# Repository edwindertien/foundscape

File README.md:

# foundscape
midi control of things that tap and go boink. The basic structure consists of a midi-interface that takes data from Ableton (or similar) and sends events to 'dimmer cards' - being called like that because initially they mostly controlled LED light. 

Two behaviours exist on the main board right now which can be set using a small dip switch: either pulse-lenght or pwm duty cycle as third 'velocity' argument in a MIDI command. 

current version (still in operation) uses an ATmega328 (started out with the ATmega8 and then the ATmega88 in WinAVR. now it uses the Arduino environment). In the meantime a version has been made using Teensy, but has not been further pursued / produces (when Teensies were made of nonobtanium). On the wishlist a new version with pico

## modules
- [actuators](./actuators/) 3D printfiles for solenoid holders
- [atmegaDimmer](./atmegaDimmer/) first generation dimmer/control box, using RS485(dynamixel) protocol, using ATmega328
- [RS485adapter](./RS485adapter/) RS485 - midi interface using ATmega32U4 (Arduino micro, native USB)
- [teensyDimmer](./teensyDimmer/) update of dimmer/control box, using Teensy 4.0. build, not tested
- [picoDimmer](./picoDimmer/) new (to be designed) version of the dimmer/control box using RPI Pico 2040/2350

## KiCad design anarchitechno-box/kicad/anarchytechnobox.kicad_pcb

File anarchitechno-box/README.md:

# foundscape electronics

## anarchitechno box (formerly known as 'pico dimmer')

The boxes are still called 'dimmer' since all channels can either be switched (solenoids, pneumatic valves) where the control parameter is a pulse duration (so short sharp tap or long, plungy tap - and everything in between) or a PWM value (used typically for LED brightness or motor velocity),

During a session at Koppelting (Amersfoort) in August 2025 we found that a very interesting additiion in just 'dimming' channels is also PWM (frequency) control and AWG / synthesis to make actuators sound even more. During the session the requirements below have been updated and start has been made with a new (schematic) design. 

On the wishlist for the next design (using for example the atmega version or the teensy version as starting point)

### power
- multiple voltages for output, would be nice to change per channel, but for now typically 1 output voltage (i.e. 12V) per channel is fine. It would be nice when the system can work on 12V, but also as low as 5V and at least at 24V
- 8 channels, individual control mode per channel for one-shot (solenoids, timing), PWM (frequency, duty cycle) and AWG (saw/sine/triangle/block/noise, frequency, phase, amplitude)
- polyfuse per channel, Fuse indicator
- 1 LED per channel (indication)
- flyback diodes per channel
- TVS, power supply protection, main fuse

not yet implemented but nice to have
- power monitoring (voltage / current)
- reverse voltage protection

For now the output section consisting of IRFZ44 and TC4423 has been working ok. Might be room to revise for newer, cheaper and SMD version. See if gate driver is necessary, but might be for higher switching frequencies. I checked other gate drivers, so far the 4427 seems a good (SMD) follow up with a good balance in price, performance and size

### power
Right now I tend to put in a Traco power TC2450 or similar to do the 12-24V to 5V conversion. Might be up for a change too. 

It wouls be very welcome to have galvanic separation between the power stage (12-24V side) and the logic side. The power consumption at the logic side is non-neglegible:
- pico (3.3V) - 20 mA? 
- OLED .. mA
- WS5500 .. mA
- USB Host -> 500mA

It might be best to build a 5Watt (1A) switching power supply or use a ready to go module. The TI 6505B uses a separate transformer (suggested, but need to be checked ) [wurth](https://octopart.com/750313974-wurth+electronics+midcom-49417564) and can go up to 5 Watt.

### galvanic separation
- using isolators it is important to separate the high/power (24V) side from the logic side. This means digital isolators as well as an isiolated 5V->5.5V supply. The USB Host needs 5V, the pico can do 5V->3.3V with its on-board converter

### brains
- pico (2W) - might be the standard board, or just the RP2040 or RP2350 chip + necessary peripherals
- OLED (small 32x128 pix) is very useful for menu, status info etc
- incremental encoder (3 switches) - pio code works fine. good for changing menu options
- simple basic LEDs on power and communication lines (so you can always check com, also when you are fiddeling with a menu), also from a distance. 
- WS8211 RGB leds (string), 1 per channel (channel mode selection) and communication status (per socket / unit)

### connection
- USB (midi, serial)  -> existing USB micro
- USB Host (midi, gamepad, HID) -> add USB A socket. Think about necessary series resistors and power components. 
- RS485 (DMX: neutrix 3/5 pin, 'dynamixel' bus) -> 3way(A, B, GND) and 4way (A, B, Power, GND) jst socket. For (my) RJ45 and a neutrik socket we can make an adapter? Or have the RJ45 system since it is so easy to stack through.. 
- ethernet: WSD5500 + socket + mag
- MIDI: old fashioned 5-pin DIN midi (CNY138 optocoupler) (can also be adapter cable from 5-way jst socket)
- A pico could in theory also do everything WIFI / Bluetooth / BLE wise. .. 
- HW sync input (optocoupler?)

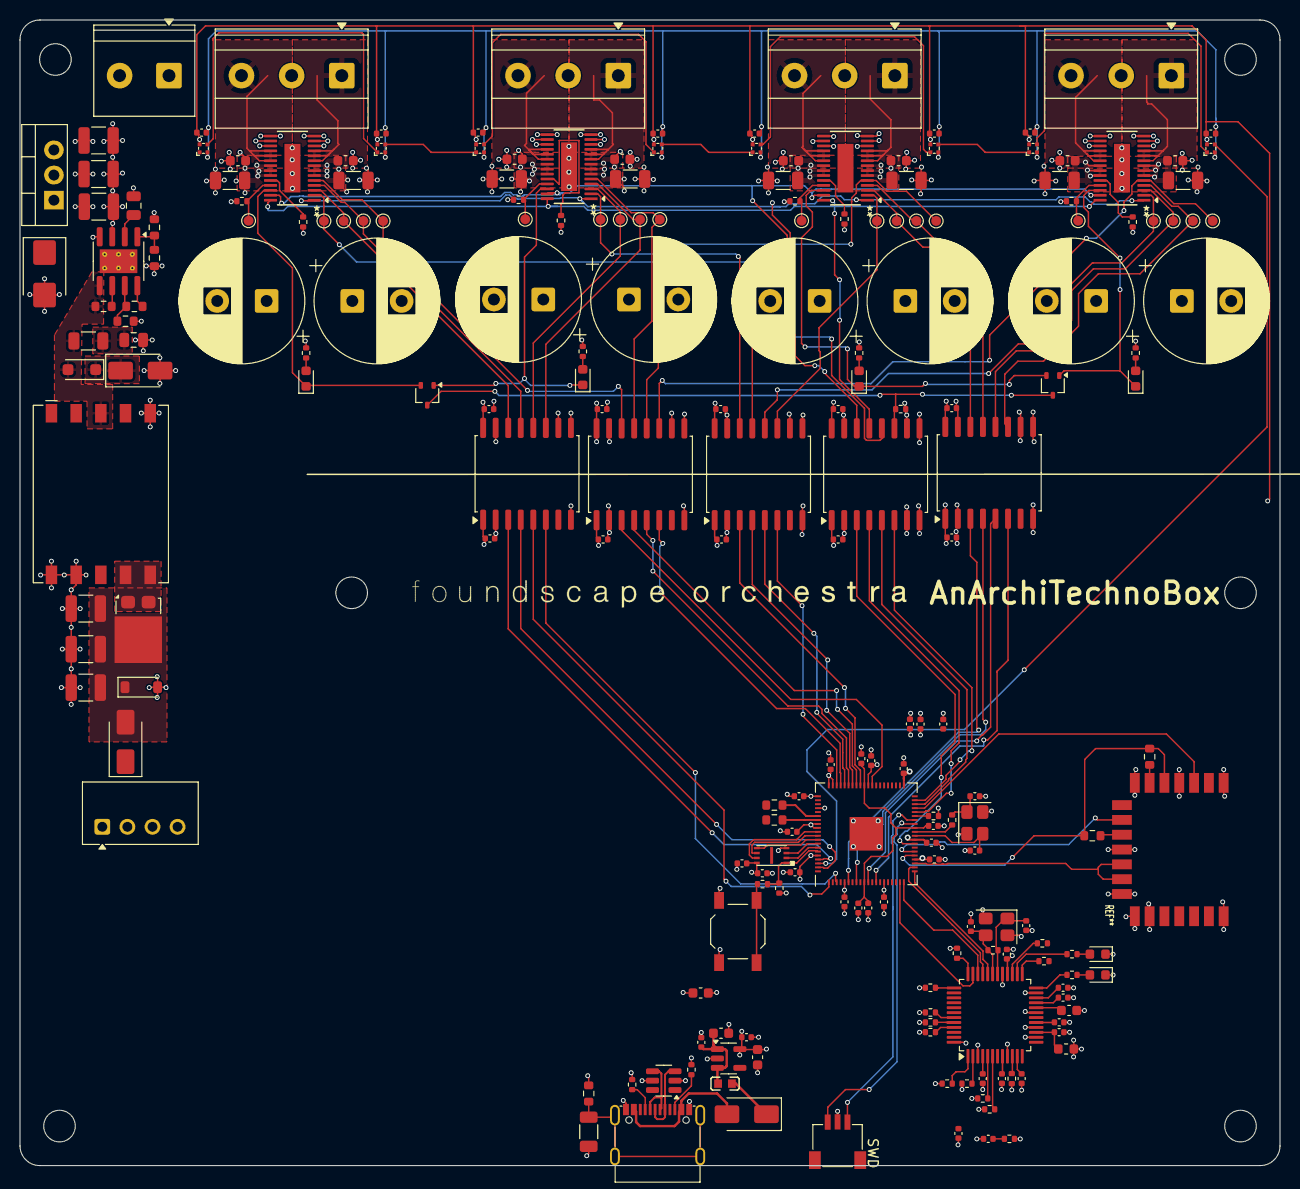
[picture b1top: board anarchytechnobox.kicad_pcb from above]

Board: 4 copper layers, 127.6 x 116.0 mm, 216 parts (0 on the bottom side), 144 nets.

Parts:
C1, C2, C3, C4, C5, C7, C8, C11, C13, C14, C15, C16, C21, C22, C23, C27, C30, C31, C32, C33, C46, C47, C48, C49, C50, C51, C54, C55, C56, C58, C60, C61, C62, C86, C87, C88, C89, C90, C91: 100nF; C_0402_1005Metric
C6: 4.7u; C_0402_1005Metric
C9, C17: 100n; C_0402_1005Metric
C10, C18, C19: 1u; C_0402_1005Metric
C12, C20, C26: 10uF; C_0603_1608Metric
C24: 4.7n 100v; C_1206_3216Metric
C25: 0.1uF; C_0402_1005Metric
C28, C29: 27p; C_0402_1005Metric
C34, C35, C40, C41, C74, C75, C80, C81: 1uF 50V; C_0603_1608Metric
C36, C37, C42, C43, C76, C77, C82, C83: 10uF 50V; C_1206_3216Metric
C38, C39, C44, C45, C78, C79, C84, C85: 1000uF 50V; CP_Radial_D12.5mm_P5.00mm
C52, C53: 15p; C_0402_1005Metric
C57: 10nF; C_0402_1005Metric
C59: 4.7uF; C_0603_1608Metric
C63: 22n; C_0402_1005Metric
C64: 10n; C_0402_1005Metric
C65: 330uF 50V; C_1210_3225Metric
C66, C67: 10uF 50V; C_1210_3225Metric
C68: 1uF 25V; C_0805_2012Metric
C69: 220pF; C_0805_2012Metric
C70, C71, C72: 47uF 10V; C_1210_3225Metric
D1: SM6T24A; D_SMB
D2, D3, D18, D19, D20, D21, D22, D23: C5349953; XL-1010
D4, D5: BAT54AW; SOT-323_SC-70
D6, D7, D8, D9, D14, D15: RED; LED_0603_1608Metric
D10: SMAJ18A; D_SMA
D11: CMMSH1-100; D_SOD-123F
D12: V8PM10SHM3/I; TO-277A
D13: CMHZ5232B; D_SOD-123
D16, D17: SS34; D_SMA
FB1: BLM18PG121SN1D; L_0603_1608Metric
H1, H2, H3, H4, H5, H6: MountingHole; MountingHole_3.2mm_M3
J1: C2988369; USB-C C2988369
J2: Conn_01x03_Socket; SWD_TOP
J3, J4, J5, J6: Screw_Terminal_01x03; TerminalBlock_Phoenix_MKDS-1,5-3-5.08_1x03_P5.08mm_Horizont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
J7: Screw_Terminal_01x02; TerminalBlock_Phoenix_PT-1,5-2-5.0-H_1x02_P5.00mm_Horizontal
L1: BLM18PG121SN1D_C14709; L0603
Q1: 12mhz; Crystal_SMD_SeikoEpson_TSX3225-4Pin_3.2x2.5mm
R1: 470; R_0603_1608Metric
R2: 10k; R_0603_1608Metric
R3: 1M; R_0603_1608Metric
R4, R5: 5.1k; R_0402_1005Metric
R6, R10: 10k; R_0402_1005Metric
R7, R8: 27; R_0603_1608Metric
R9, R11: 1k; R_0402_1005Metric
R12, R15, R25, R26, R27, R28, R41, R44: 470R; R_0402_1005Metric
R13, R16, R42, R45: 0R; R_0402_1005Metric
R14, R17, R43, R46: TBD; R_0402_1005Metric
R18: 10K; R_0402_1005Metric
R19: 1MEG; R_0402_1005Metric
R20, R21, R22, R23, R24: 1K; R_0402_1005Metric
R29: 12.4k; R_0402_1005Metric
R30, R31, R33, R34: 49R9; R_0402_1005Metric
R32: 10R; R_0402_1005Metric
R35: 1MEG; R_0603_1608Metric
R36: 200K; R_0603_1608Metric
R37: 150K; R_0603_1608Metric
R38: 113K; R_0603_1608Metric
R39: 100R; R_1206_3216Metric
R40: 10K; R_0603_1608Metric
SW1: C318884; SW_SPST_TL3342
TP1, TP2, TP3, TP4, TP5, TP6, TP7, TP8, TP9, TP10, TP11, TP12, TP13, TP14, TP15, TP16, TP17, TP18, TP19, TP20: TestPoint; TestPoint_Pad_D1.0mm
U1: TME-0503S; Converter_DCDC_TRACO_TME_03xxS_05xxS_12xxS_Single_THT
U3: LM7812_TO220; TO-220-3_Vertical
U4: <value>; rpi_rmc20452t
U5: LP5907MFX-3.3; SOT-23-5
U7: C85364; SOT-23-6
U8: QFN-80_EP_10x10_Pitch0.4mm
U9, U10, U13, U14: ISO7740DWR; SOIC-16W_7.5x10.3mm_P1.27mm
U11, U12, U20, U21: DRV8243SQDGQRQ1; TI_HVSSOP-28
U15: ISO7742DWR; SOIC-16W_7.5x10.3mm_P1.27mm
U16: W5500; LQFP-48_7x7mm_P0.5mm
U18: ADPL54203ES8E#PBF; SOIC-8-1EP_3.9x4.9mm_P1.27mm_EP2.41x3.81mm_ThermalVias
U19: 750311564; T_Wurth_WE-FB-EP13_16.36
U$1: C2843335 W25Q16JVUXIQ; USON-8-EP(2x3)
Y1: 25MHz; Crystal_SMD_3225-4Pin_3.2x2.5mm

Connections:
+1V1: C18.2, C19.1, C21.1, C22.2, C23.1, U8.10 (DVDD), U8.32 (DVDD), U8.51 (DVDD)
+3.3VA: C55.1, C56.1, C58.1, C60.1, C61.1, C62.1, FB1.2, U16.4 (AVDD), U16.8 (AVDD), U16.11 (AVDD), U16.15 (AVDD), U16.17 (AVDD), U16.21 (AVDD)
+3.3VP: C31.1, C33.1, C49.1, C50.1, C51.1, R12.1, R13.1, R15.1, R16.1, R18.1, R41.1, R42.1, R44.1, R45.1, U9.10 (EN2), U9.16 (VCC2), U10.10 (EN2), U10.16 (VCC2), U13.10 (EN2), U13.16 (VCC2), U14.10 (EN2), U14.16 (VCC2), U15.10 (EN2), U15.16 (VCC2)
+3V3: C1.2, C2.2, C3.2, C4.2, C5.2, C6.1, C7.2, C8.2, C10.2, C11.2, C13.2, C14.2, C15.2, C16.2, C17.2, C20.1, C25.1, C26.1, C27.2, C30.1, C32.1, C46.1, C47.1, C48.1, C54.1, C86.2, C87.2, C88.2, C89.2, C90.2, C91.2, D2.2 (VDD), D3.2 (VDD), D18.2 (VDD), D19.2 (VDD), D20.2 (VDD), D21.2 (VDD), D22.2 (VDD), D23.2 (VDD), FB1.1, R6.2, R10.1, R20.1, R21.1, R22.1, R23.2, R24.2, R30.1, R31.1, R32.1, R33.1, R34.1, U4.14 (VDDIO), U4.16 (VIN), U5.5 (OUT), U7.5 (REF), U8.5 (IOVDD), U8.15 (IOVDD), U8.24 (IOVDD), U8.29 (IOVDD), U8.41 (IOVDD), U8.50 (IOVDD), U8.59 (ADC_IOVDD), U8.60 (IOVDD), U8.61 (VREG_AVDD), U8.64 (VREG_VIN), U8.68 (USB_OTP_VDD), U8.69 (QSPI_IOVDD), U8.76 (IOVDD), U9.1 (VCC1), U10.1 (VCC1), U13.1 (VCC1), U14.1 (VCC1), U15.1 (VCC1), U15.7 (EN1), U16.28 (VDD), U$1.8 (VCC)
+5V: D16.1 (K), D17.1 (K), L1.1, U1.2 (+Vin)
+24V: D1.1 (A1), U3.1 (VI)
+VDC: C34.1, C35.1, C36.1, C37.1, C38.1, C39.1, C40.1, C41.1, C42.1, C43.1, C44.1, C45.1, C65.1 (+), C66.1 (+), C67.1 (+), C69.1 (+), C74.1, C75.1, C76.1, C77.1, C78.1, C79.1, C80.1, C81.1, C82.1, C83.1, C84.1, C85.1, D10.2 (A), J7.1, R35.2 (-), U11.6 (VM), U11.7 (VM), U11.8 (VM), U11.21 (VM), U11.22 (VM), U11.23 (VM), U12.6 (VM), U12.7 (VM), U12.8 (VM), U12.21 (VM), U12.22 (VM), U12.23 (VM), U18.3 (VIN), U19.5 (N1_2), U20.6 (VM), U20.7 (VM), U20.8 (VM), U20.21 (VM), U20.22 (VM), U20.23 (VM), U21.6 (VM), U21.7 (VM), U21.8 (VM), U21.21 (VM), U21.22 (VM), U21.23 (VM)
/DCDC Flyback/PRE_5V: C70.1 (+), C71.1 (+), C72.1 (+), D12.3 (K), D13.1 (K), D17.2 (A)
/DCDC Flyback/PRE_PRE_5V: D12.1 (A), D12.2 (A), U19.6 (N2_1), U19.7 (N2_1)
/DCDC Flyback/VDC_CAPRES: C69.2 (-), R39.1 (+)
/DCDC Flyback/VDC_DIODES: D10.1 (K), D11.1 (K)
/DCDC Flyback/VDC_SW: D11.2 (A), R37.2 (-), R39.2 (-), U18.5 (SW), U19.3 (N1_1)
/Ethernet/ETH_RX_M: R34.2, U16.5 (RXN)
/Ethernet/ETH_RX_P: R33.2, U16.6 (RXP)
/Ethernet/ETH_TX_M: R31.2, U16.1 (TXN)
/Ethernet/ETH_TX_P: R30.2, U16.2 (TXP)
/Ethernet/SPI_CS: U8.21 (GPIO21), U16.32 (~SCS)
/Ethernet/SPI_INT: R23.1, U16.36 (~INT)
/Ethernet/SPI_MISO: U8.20 (GPIO20), U16.34 (MISO)
/Ethernet/SPI_MOSI: U8.19 (GPIO19), U16.35 (MOSI)
/Ethernet/SPI_RST: R24.1, U16.37 (~RST)
/Ethernet/SPI_SCK: U8.22 (GPIO22), U16.33 (SCLK)
/HB_1_OUT_A: J3.1, U20.9 (OUT1), U20.10 (OUT1), U20.11 (OUT1)
/HB_1_OUT_B: J3.3, U20.18 (OUT2), U20.19 (OUT2), U20.20 (OUT2)
/HB_1_OUT_C: J4.1, U21.9 (OUT1), U21.10 (OUT1), U21.11 (OUT1)
/HB_1_OUT_D: J4.3, U21.18 (OUT2), U21.19 (OUT2), U21.20 (OUT2)
/HB_2_OUT_A: J5.1, U11.9 (OUT1), U11.10 (OUT1), U11.11 (OUT1)
/HB_2_OUT_B: J5.3, U11.18 (OUT2), U11.19 (OUT2), U11.20 (OUT2)
/HB_2_OUT_C: J6.1, U12.9 (OUT1), U12.10 (OUT1), U12.11 (OUT1)
/HB_2_OUT_D: J6.3, U12.18 (OUT2), U12.19 (OUT2), U12.20 (OUT2)
/Isolators/MCU_CS1: U8.52 (GPIO41_ADC1), U14.3 (INA)
/Isolators/MCU_CS2: U8.54 (GPIO43_ADC3), U14.4 (INB)
/Isolators/MCU_CS3: U8.56 (GPIO45_ADC5), U14.5 (INC)
/Isolators/MCU_CS4: U8.58 (GPIO47_ADC7), U14.6 (IND)
/Isolators/MCU_DRV_nFAULT_COMMON: U8.39 (GPIO31), U15.6 (OUTD)
/Isolators/MCU_PWM_A_OFF: U8.49 (GPIO40_ADC0), U13.3 (INA)
/Isolators/MCU_PWM_B_OFF: U8.53 (GPIO42_ADC2), U13.4 (INB)
/Isolators/MCU_PWM_C_OFF: U8.55 (GPIO44_ADC4), U13.5 (INC)
/Isolators/MCU_PWM_D_OFF: U8.57 (GPIO46_ADC6), U13.6 (IND)
/Isolators/MCU_SPI_CLK: U8.28 (GPIO27), U15.3 (INA)
/Isolators/MCU_SPI_MISO: U8.38 (GPIO30), U15.5 (OUTC)
/Isolators/MCU_SPI_MOSI: U8.36 (GPIO28), U15.4 (INB)
/Isolators/PWR_DRV_nFAULT_COMMON: D4.3, D5.3, R18.2, U15.11 (IND)
/Isolators/PWR_PWM_A_OFF: TP19.1, U13.14 (OUTA), U21.5 (DRVOFF)
/Isolators/PWR_PWM_B_OFF: TP14.1, U13.13 (OUTB), U20.5 (DRVOFF)
/Isolators/PWR_PWM_C_OFF: TP9.1, U12.5 (DRVOFF), U13.12 (OUTC)
/Isolators/PWR_PWM_D_OFF: TP4.1, U11.5 (DRVOFF), U13.11 (OUTD)
/Isolators/PWR_SPI_CLK: U11.1 (SCLK), U12.1 (SCLK), U15.14 (OUTA), U20.1 (SCLK), U21.1 (SCLK)
/Isolators/PWR_SPI_CS1: TP15.1, U14.14 (OUTA), U20.2 (nSCS)
/Isolators/PWR_SPI_CS2: TP20.1, U14.13 (OUTB), U21.2 (nSCS)
/Isolators/PWR_SPI_CS3: TP5.1, U11.2 (nSCS), U14.12 (OUTC)
/Isolators/PWR_SPI_CS4: TP10.1, U12.2 (nSCS), U14.11 (OUTD)
/Isolators/PWR_SPI_MISO: U11.27 (SDO), U12.27 (SDO), U15.12 (INC), U20.27 (SDO), U21.27 (SDO)
/Isolators/PWR_SPI_MOSI: U11.28 (SDI), U12.28 (SDI), U15.13 (OUTB), U20.28 (SDI), U21.28 (SDI)
/LED_STRING: D2.4 (DI), U8.78 (GPIO1)
/RP2350BMCU/5V_filtered: C9.2, C12.1, L1.2, U5.1 (IN), U5.3 (EN)
/RP2350BMCU/BOOTSEL_BUT: R9.2, SW1.2
/RP2350BMCU/BREAKOUT_5V: D16.2 (A), J1.A4B9 (VBUS), J1.A9B4 (VBUS)
/RP2350BMCU/MEM_CLK: U8.71 (QSPI_SCLK), U$1.6 (CLK)
/RP2350BMCU/MEM_CS: R6.1, R9.1, U8.75 (QSPI_SS), U$1.1 (/CS)
/RP2350BMCU/MEM_IO0: U8.72 (QSPI_SD0), U$1.5 (DI)
/RP2350BMCU/MEM_IO1: U8.74 (QSPI_SD1), U$1.2 (DO)
/RP2350BMCU/MEM_IO2: U8.73 (QSPI_SD2), U$1.3 (IO2)
/RP2350BMCU/MEM_IO3: U8.70 (QSPI_SD3), U$1.7 (IO3)
/RP2350BMCU/PMW1_A: U8.79 (GPIO2), U9.4 (INB)
/RP2350BMCU/PWM0_A: U8.77 (GPIO0), U9.3 (INA)
/RP2350BMCU/PWM2_A: U8.1 (GPIO4), U9.5 (INC)
/RP2350BMCU/PWM3_A: U8.3 (GPIO6), U9.6 (IND)
/RP2350BMCU/PWM4_A: U8.6 (GPIO8), U10.3 (INA)
/RP2350BMCU/PWM5_A: U8.8 (GPIO10), U10.4 (INB)
/RP2350BMCU/PWM6_A: U8.11 (GPIO12), U10.5 (INC)
/RP2350BMCU/PWM7_A: U8.13 (GPIO14), U10.6 (IND)
/RP2350BMCU/RUN: R10.2, U8.35 (RUN)
/RP2350BMCU/SWCLK: J2.1, U8.33 (SWCLK)
/RP2350BMCU/SWDIO: J2.3, U8.34 (SWD)
/RP2350BMCU/USB_N: J1.A7 (DN1), J1.B7 (DN2), R8.1, U7.4 (IO3)
/RP2350BMCU/USB_P: J1.A6 (DP1), J1.B6 (DP2), R7.1, U7.3 (IO2)
/RP2350BMCU/USB_PRE_N: R8.2, U8.66 (USB_DN)
/RP2350BMCU/USB_PRE_P: R7.2, U8.67 (USB_DP)
/RP2350BMCU/WIFI_23: U4.12 (WL_ON), U4.13 (BT_ON), U8.23 (GPIO23)
/RP2350BMCU/WIFI_24: R1.2, R2.2, U4.5 (DI), U8.25 (GPIO24)
/RP2350BMCU/WIFI_25: U4.9 (CS), U8.26 (GPIO25)
/RP2350BMCU/WIFI_29: U4.3 (SCLK), U8.37 (GPIO29)
/TwoIsolatedFETs0/HBridge_A/DRV_ISENSE: R46.1, TP16.1, U21.25 (IPROPI)
/TwoIsolatedFETs0/HBridge_A/DRV_nFAULT: D4.2, D15.1 (K), U21.26 (nFAULT)
/TwoIsolatedFETs0/HBridge_B/DRV_ISENSE: R43.1, TP11.1, U20.25 (IPROPI)
/TwoIsolatedFETs0/HBridge_B/DRV_nFAULT: D4.1, D14.1 (K), U20.26 (nFAULT)
/TwoIsolatedFETs0/PWM_A_1: TP18.1, U9.13 (OUTB), U21.4 (EN/IN1)
/TwoIsolatedFETs0/PWM_A_2: TP17.1, U9.14 (OUTA), U21.3 (PH/IN2)
/TwoIsolatedFETs0/PWM_B_1: TP13.1, U9.11 (OUTD), U20.4 (EN/IN1)
/TwoIsolatedFETs0/PWM_B_2: TP12.1, U9.12 (OUTC), U20.3 (PH/IN2)
/TwoIsolatedFETs1/HBridge_A/DRV_ISENSE: R17.1, TP6.1, U12.25 (IPROPI)
/TwoIsolatedFETs1/HBridge_A/DRV_nFAULT: D5.2, D7.1 (K), U12.26 (nFAULT)
/TwoIsolatedFETs1/HBridge_B/DRV_ISENSE: R14.1, TP1.1, U11.25 (IPROPI)
/TwoIsolatedFETs1/HBridge_B/DRV_nFAULT: D5.1, D6.1 (K), U11.26 (nFAULT)
/TwoIsolatedFETs1/PWM_A_1: TP8.1, U10.13 (OUTB), U12.4 (EN/IN1)
/TwoIsolatedFETs1/PWM_A_2: TP7.1, U10.14 (OUTA), U12.3 (PH/IN2)
/TwoIsolatedFETs1/PWM_B_1: TP3.1, U10.11 (OUTD), U11.4 (EN/IN1)
/TwoIsolatedFETs1/PWM_B_2: TP2.1, U10.12 (OUTC), U11.3 (PH/IN2)
GND: C1.1, C2.1, C3.1, C4.1, C5.1, C6.2, C7.1, C8.1, C9.1, C10.1, C11.1, C12.2, C13.1, C14.1, C15.1, C16.1, C17.1, C18.1, C19.2, C20.2, C21.2, C22.1, C23.2, C24.1, C25.2, C26.2, C27.1, C28.2, C29.2, C30.2, C32.2, C46.2, C47.2, C48.2, C52.2, C53.2, C54.2, C55.2, C56.2, C57.2, C58.2, C59.2, C60.2, C61.2, C62.2, C63.1, C64.1, C70.2 (-), C71.2 (-), C72.2 (-), C86.1, C87.1, C88.1, C89.1, C90.1, C91.1, D2.3 (GND), D3.3 (GND), D8.1 (K), D9.1 (K), D13.2 (A), D18.3 (GND), D19.3 (GND), D20.3 (GND), D21.3 (GND), D22.3 (GND), D23.3 (GND), J1.A1B12 (GND), J1.A12B1 (GND), J2.2, Q1.2 (G2), Q1.4 (G1), R3.1, R4.2, R5.2, R29.2, SW1.1, U1.3 (-Vout), U4.1 (GND), U4.4 (GND), U4.7 (GND), U4.11 (GND), U4.15 (GND), U4.21 (GND), U5.2 (GND), U7.2 (GND), U8.81 (GND), U9.2 (GND1), U9.8 (GND1), U10.2 (GND1), U10.8 (GND1), U13.2 (GND1), U13.8 (GND1), U14.2 (GND1), U14.8 (GND1), U15.2 (GND1), U15.8 (GND1), U16.3 (AGND), U16.9 (AGND), U16.14 (AGND), U16.16 (AGND), U16.19 (AGND), U16.23 (RSVD), U16.29 (GND), U16.48 (AGND), U19.9 (N2_2), U19.10 (N2_2), U$1.4 (GND), Y1.2, Y1.4
GND2: C31.2, C33.2, C34.2, C35.2, C36.2, C37.2, C38.2, C39.2, C40.2, C41.2, C42.2, C43.2, C44.2, C45.2, C49.2, C50.2, C51.2, C65.2 (-), C66.2 (-), C67.2 (-), C68.2 (-), C74.2, C75.2, C76.2, C77.2, C78.2, C79.2, C80.2, C81.2, C82.2, C83.2, C84.2, C85.2, D1.2 (A2), J3.2, J4.2, J5.2, J6.2, J7.2, R14.2, R17.2, R36.1 (+), R40.2 (-), R43.2, R46.2, U1.1 (-Vin), U3.2 (GND), U9.9 (GND2), U9.15 (GND2), U10.9 (GND2), U10.15 (GND2), U11.12 (GND), U11.13 (GND), U11.14 (GND), U11.15 (GND), U11.16 (GND), U11.17 (GND), U11.EP (GND), U12.12 (GND), U12.13 (GND), U12.14 (GND), U12.15 (GND), U12.16 (GND), U12.17 (GND), U12.EP (GND), U13.9 (GND2), U13.15 (GND2), U14.9 (GND2), U14.15 (GND2), U15.9 (GND2), U15.15 (GND2), U18.4 (GND), U18.9 (GND), U20.12 (GND), U20.13 (GND), U20.14 (GND), U20.15 (GND), U20.16 (GND), U20.17 (GND), U20.EP (GND), U21.12 (GND), U21.13 (GND), U21.14 (GND), U21.15 (GND), U21.16 (GND), U21.17 (GND), U21.EP (GND)
unnamed: C24.2, J1.SHELL1, J1.SHELL2, J1.SHELL3, J1.SHELL4, R3.2
unnamed: C68.1 (+), U18.2 (INTVCC)
unnamed: D2.1 (DO), D3.4 (DI)
unnamed: D6.2 (A), R12.2
unnamed: D7.2 (A), R15.2
unnamed: D8.2 (A), R25.2
unnamed: D9.2 (A), R27.2
unnamed: D14.2 (A), R41.2
unnamed: D15.2 (A), R44.2
unnamed: D3.1 (DO), D18.4 (DI)
unnamed: D18.1 (DO), D19.4 (DI)
unnamed: D19.1 (DO), D20.4 (DI)
unnamed: D20.1 (DO), D21.4 (DI)
unnamed: D21.1 (DO), D22.4 (DI)
unnamed: D22.1 (DO), D23.4 (DI)
unnamed: J1.A5 (CC1), R4.1
unnamed: J1.B5 (CC2), R5.1
unnamed: C28.1, Q1.1 (X1), R11.1
unnamed: C29.1, Q1.3 (X2), U8.30 (XIN)
unnamed: R35.1 (+), R36.2 (-), U18.1 (EN/UVLO)
unnamed: R37.1 (+), U18.6 (RFB)
unnamed: R38.1 (+), U18.8 (TC)
unnamed: R38.2 (-), R40.1 (+), U18.7 (RREF)
unnamed: R1.1, U4.6 (DO)
unnamed: R2.1, U4.10 (nIRQ)
unnamed: R11.2, U8.31 (XOUT)
unnamed: R13.2, U11.24 (nSLEEP)
unnamed: R16.2, U12.24 (nSLEEP)
unnamed: C57.1, U16.22 (1V2O)
unnamed: R28.1, U16.27 (ACTLED)
unnamed: R27.1, U16.26 (DUPLED)
unnamed: R29.1, U16.10 (EXRES1)
unnamed: R26.1, U16.25 (LINKLED)
unnamed: R20.2, U16.45 (PMODE0)
unnamed: R21.2, U16.44 (PMODE1)
unnamed: R22.2, U16.43 (PMODE2)
unnamed: R25.1, U16.24 (SPDLED)
unnamed: C59.1, U16.20 (TOCAP)
unnamed: C52.1, R19.2, U16.30 (XI/CLKIN), Y1.1
unnamed: C53.1, R19.1, U16.31 (XO), Y1.3
unnamed: C63.2, R32.2
unnamed: R42.2, U20.24 (nSLEEP)
unnamed: R45.2, U21.24 (nSLEEP)

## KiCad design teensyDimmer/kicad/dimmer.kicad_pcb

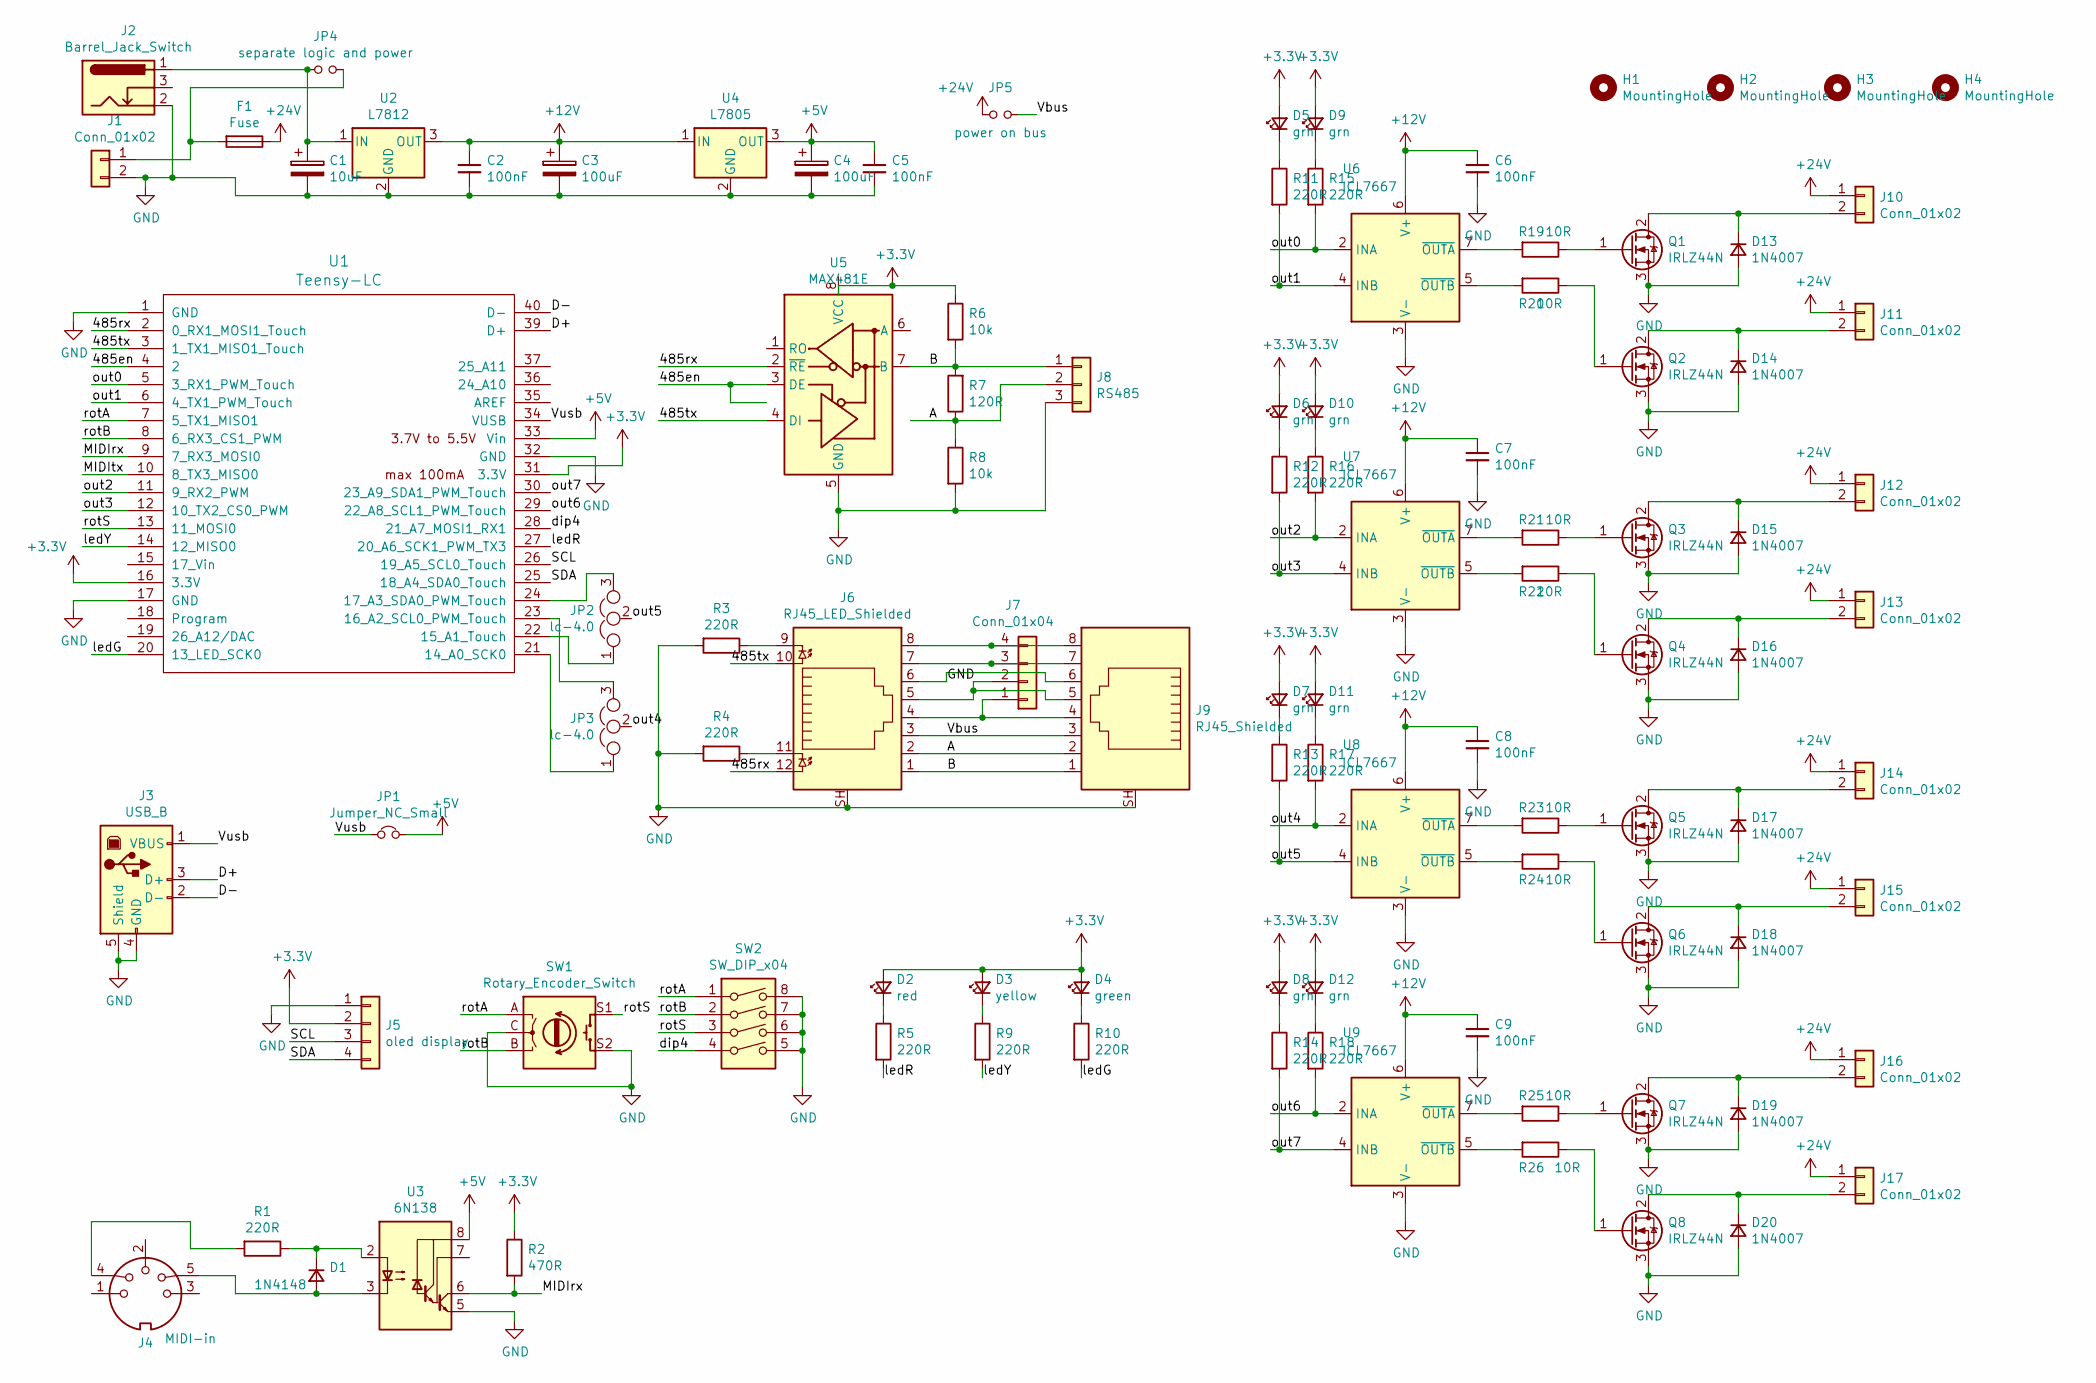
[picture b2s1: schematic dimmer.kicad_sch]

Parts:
C1: 10uF; CP_Radial_D5.0mm_P2.50mm
C2, C5: 100nF; C_Disc_D5.0mm_W2.5mm_P5.00mm
C3, C4: 100uF; CP_Radial_D6.3mm_P2.50mm
C6, C7, C8, C9: 100nF; C_Disc_D3.0mm_W2.0mm_P2.50mm
D1: 1N4148; D_DO-34_SOD68_P7.62mm_Horizontal
D2: red; LED_D3.0mm
D3: yellow; LED_D3.0mm
D4: green; LED_D3.0mm
D5, D6, D7, D8, D9, D10, D11, D12: grn; LED_D3.0mm
D13, D14, D15, D16, D17, D18, D19, D20: 1N4007; D_A-405_P7.62mm_Horizontal
F1: Fuse; Fuse_Bourns_MF-RHT300
H1, H2, H3, H4: MountingHole; MountingHole_3.2mm_M3
J1, J10, J11, J12, J13, J14, J15, J16, J17: Conn_01x02; PhoenixContact_MC_1,5_2-G-3.81_1x02_P3.81mm_Horizontal
J2: Barrel_Jack_Switch; BarrelJack_Horizontal
J3: USB_B; USB_A
J4: MIDI-in; PinHeader_1x05_P2.54mm_Vertical
J5: oled display; PinHeader_1x04_P2.54mm_Vertical
J6: RJ45_LED_Shielded; RJ45_Amphenol_RJHSE538X
J7: Conn_01x04; PinHeader_1x04_P2.54mm_Vertical
J8: RS485; PinHeader_1x03_P2.54mm_Vertical
J9: RJ45_Shielded; RJ45_Amphenol_RJHSE538X
JP1: Jumper_NC_Small; SolderJumper-2_P1.3mm_Bridged_RoundedPad1.0x1.5mm
JP2, JP3: lc-4.0; SolderJumper-3_P1.3mm_Bridged12_RoundedPad1.0x1.5mm
JP4: separate logic and power; PinHeader_1x02_P2.54mm_Vertical
JP5: power on bus; PinHeader_1x02_P2.54mm_Vertical
Q1, Q2, Q3, Q4, Q5, Q6, Q7, Q8: IRLZ44N; TO-220-3_Horizontal_TabUp
R1, R3, R4, R5, R9, R10, R11, R12, R13, R14, R15, R16, R17, R18: 220R; R_Axial_DIN0207_L6.3mm_D2.5mm_P7.62mm_Horizontal
R2: 470R; R_Axial_DIN0207_L6.3mm_D2.5mm_P7.62mm_Horizontal
R6, R8: 10k; R_Axial_DIN0207_L6.3mm_D2.5mm_P7.62mm_Horizontal
R7: 120R; R_Axial_DIN0207_L6.3mm_D2.5mm_P7.62mm_Horizontal
R19, R20, R21, R22, R23, R24, R25, R26: 10R; R_Axial_DIN0207_L6.3mm_D2.5mm_P7.62mm_Horizontal
SW1: Rotary_Encoder_Switch; RotaryEncoder_Alps_EC11E-Switch_Vertical_H20mm
SW2: SW_DIP_x04; DIP-8_W7.62mm
U1: Teensy-LC; Teensy_LC
U2: L7812; TO-220-3_Horizontal_TabUp
U3: 6N138; DIP-8_W7.62mm
U4: L7805; TO-220-3_Horizontal_TabUp
U5: MAX481E; DIP-8_W7.62mm
U6, U7, U8, U9: ICL7667; DIP-8_W7.62mm

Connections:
+3V3: D2.2 (A), D3.2 (A), D4.2 (A), D5.2 (A), D6.2 (A), D7.2 (A), D8.2 (A), D9.2 (A), D10.2 (A), D11.2 (A), D12.2 (A), J5.2, R2.1, R6.1, U1.16 (3.3V), U1.31 (3.3V), U5.8 (VCC)
+5V: C4.1, C5.1, JP1.2, U1.33 (Vin), U3.8 (VCC), U4.3 (OUT)
+12V: C2.1, C3.1, C6.1, C7.1, C8.1, C9.1, U2.3 (OUT), U4.1 (IN), U6.6 (V+), U7.6 (V+), U8.6 (V+), U9.6 (V+)
+24V: F1.1, J10.1, J11.1, J12.1, J13.1, J14.1, J15.1, J16.1, J17.1, JP5.1
/485tx: J6.10, U1.3 (1_TX1_MISO1_Touch), U5.4 (DI)
/A: J6.2, J8.2, J9.2, R7.1, R8.1, U5.6 (A)
/B: J6.1, J8.1, J9.1, R6.2, R7.2, U5.7 (B)
/D+: J3.3 (D+), U1.39 (D+)
/D-: J3.2 (D-), U1.40 (D-)
/MIDIrx: R2.2, U1.9 (7_RX3_MOSI0), U3.6 (VO2)
/MIDItx: U1.10 (8_TX3_MISO0)
/SCL: J5.3, U1.26 (19_A5_SCL0_Touch)
/SDA: J5.4, U1.25 (18_A4_SDA0_Touch)
/Vbus: J6.3, J9.3, JP5.2
/Vusb: J3.1 (VBUS), JP1.1, U1.34 (VUSB)
/dip4: SW2.4, U1.28 (21_A7_MOSI1_RX1)
/ledG: R10.2, U1.20 (13_LED_SCK0)
/ledR: R5.2, U1.27 (20_A6_SCK1_PWM_TX3)
/ledY: R9.2, U1.14 (12_MISO0)
/out0: R15.2, U1.5 (3_RX1_PWM_Touch), U6.2 (INA)
/out1: R11.2, U1.6 (4_TX1_PWM_Touch), U6.4 (INB)
/out2: R16.2, U1.11 (9_RX2_PWM), U7.2 (INA)
/out3: R12.2, U1.12 (10_TX2_CS0_PWM), U7.4 (INB)
/out4: JP3.2, R17.2, U8.2 (INA)
/out5: JP2.2, R13.2, U8.4 (INB)
/out6: R18.2, U1.29 (22_A8_SCL1_PWM_Touch), U9.2 (INA)
/out7: R14.2, U1.30 (23_A9_SDA1_PWM_Touch), U9.4 (INB)
/rotA: SW1.A, SW2.1, U1.7 (5_TX1_MISO1)
/rotB: SW1.B, SW2.2, U1.8 (6_RX3_CS1_PWM)
/rotS: SW1.S1, SW2.3, U1.13 (11_MOSI0)
GND: C1.2, C2.2, C3.2, C4.2, C5.2, C6.2, C7.2, C8.2, C9.2, D13.2 (A), D14.2 (A), D15.2 (A), D16.2 (A), D17.2 (A), D18.2 (A), D19.2 (A), D20.2 (A), J1.2, J2.2, J3.4 (GND), J3.5 (Shield), J5.1, J6.6, J6.SH, J8.3, J9.6, J9.SH, Q1.3 (S), Q2.3 (S), Q3.3 (S), Q4.3 (S), Q5.3 (S), Q6.3 (S), Q7.3 (S), Q8.3 (S), R3.2, R4.2, R8.2, SW1.C, SW1.S2, SW2.5, SW2.6, SW2.7, SW2.8, U1.1 (GND), U1.17 (GND), U1.32 (GND), U2.2 (GND), U3.5 (GND), U4.2 (GND), U5.5 (GND), U6.3 (V-), U7.3 (V-), U8.3 (V-), U9.3 (V-)
unnamed: C1.1, J2.1, JP4.1, U2.1 (IN)
unnamed: D1.1 (K), R1.1, U3.2 (C1)
unnamed: D1.2 (A), J4.5, U3.3 (C2)
unnamed: D2.1 (K), R5.1
unnamed: D3.1 (K), R9.1
unnamed: D4.1 (K), R10.1
unnamed: D5.1 (K), R11.1
unnamed: D6.1 (K), R12.1
unnamed: D7.1 (K), R13.1
unnamed: D8.1 (K), R14.1
unnamed: D9.1 (K), R15.1
unnamed: D10.1 (K), R16.1
unnamed: D11.1 (K), R17.1
unnamed: D12.1 (K), R18.1
unnamed: D13.1 (K), J10.2, Q1.2 (D)
unnamed: D14.1 (K), J11.2, Q2.2 (D)
unnamed: D15.1 (K), J12.2, Q3.2 (D)
unnamed: D16.1 (K), J13.2, Q4.2 (D)
unnamed: D17.1 (K), J14.2, Q5.2 (D)
unnamed: D18.1 (K), J15.2, Q6.2 (D)
unnamed: D19.1 (K), J16.2, Q7.2 (D)
unnamed: D20.1 (K), J17.2, Q8.2 (D)
unnamed: F1.2, J1.1, JP4.2
unnamed: J4.4, R1.2
unnamed: J6.4, J7.1, J9.4
unnamed: J6.5, J7.2, J9.5
unnamed: J6.7, J7.3, J9.7
unnamed: J6.8, J7.4, J9.8
unnamed: J6.9, R3.1
unnamed: J6.11, R4.1
unnamed: JP2.1, U1.22 (15_A1_Touch)
unnamed: JP2.3, U1.24 (17_A3_SDA0_PWM_Touch)
unnamed: JP3.1, U1.21 (14_A0_SCK0)
unnamed: JP3.3, U1.23 (16_A2_SCL0_PWM_Touch)
unnamed: Q1.1 (G), R19.1
unnamed: Q2.1 (G), R20.1
unnamed: Q3.1 (G), R21.1
unnamed: Q4.1 (G), R22.1
unnamed: Q5.1 (G), R23.1
unnamed: Q6.1 (G), R24.1
unnamed: Q7.1 (G), R25.1
unnamed: Q8.1 (G), R26.1
unnamed: R19.2, U6.7 (~OUTA)
unnamed: R20.2, U6.5 (~OUTB)
unnamed: R21.2, U7.7 (~OUTA)
unnamed: R22.2, U7.5 (~OUTB)
unnamed: R23.2, U8.7 (~OUTA)
unnamed: R24.2, U8.5 (~OUTB)
unnamed: R25.2, U9.7 (~OUTA)
unnamed: R26.2, U9.5 (~OUTB)

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
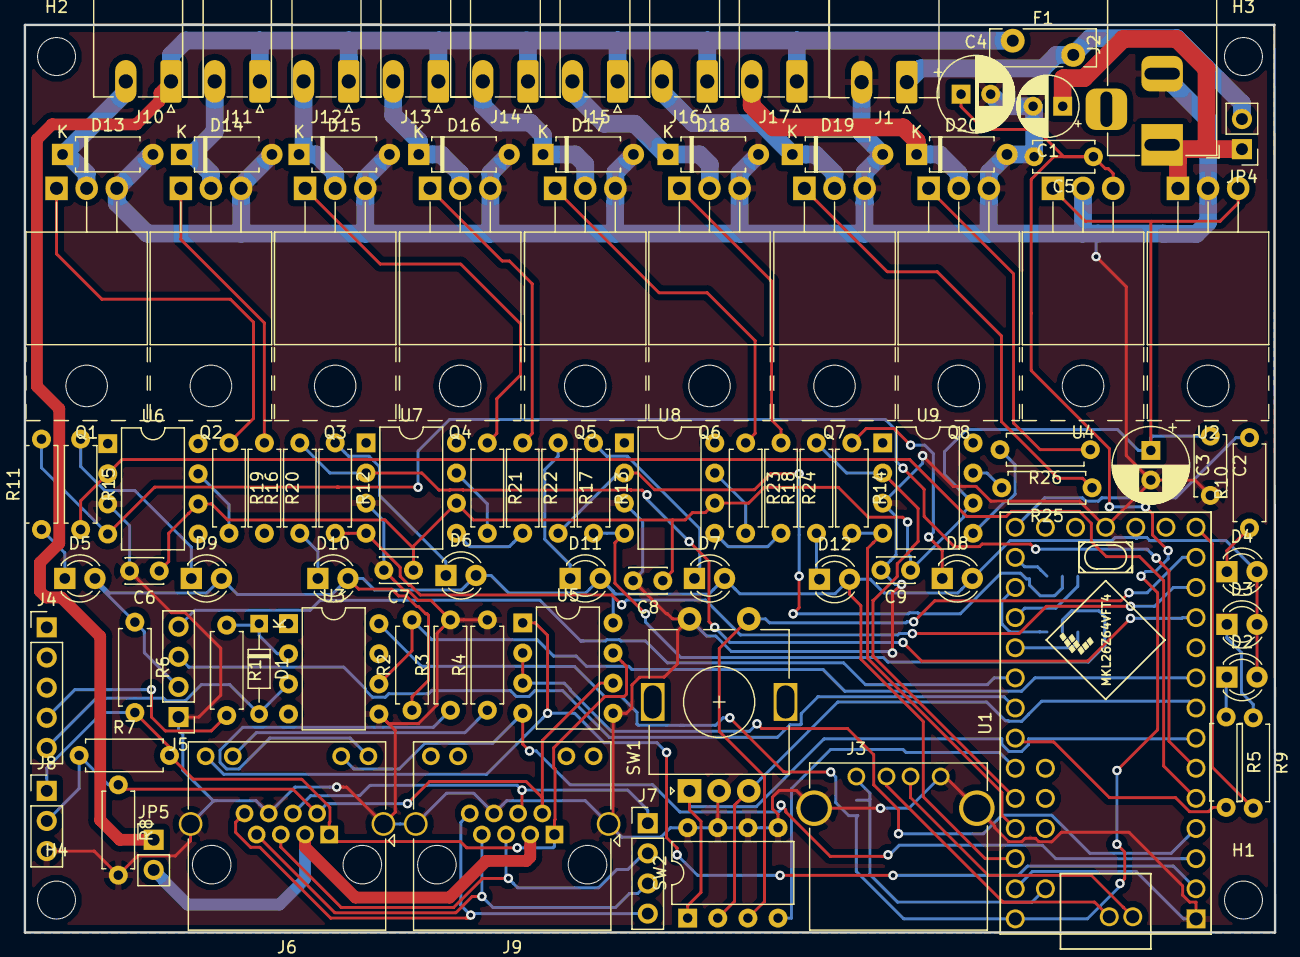
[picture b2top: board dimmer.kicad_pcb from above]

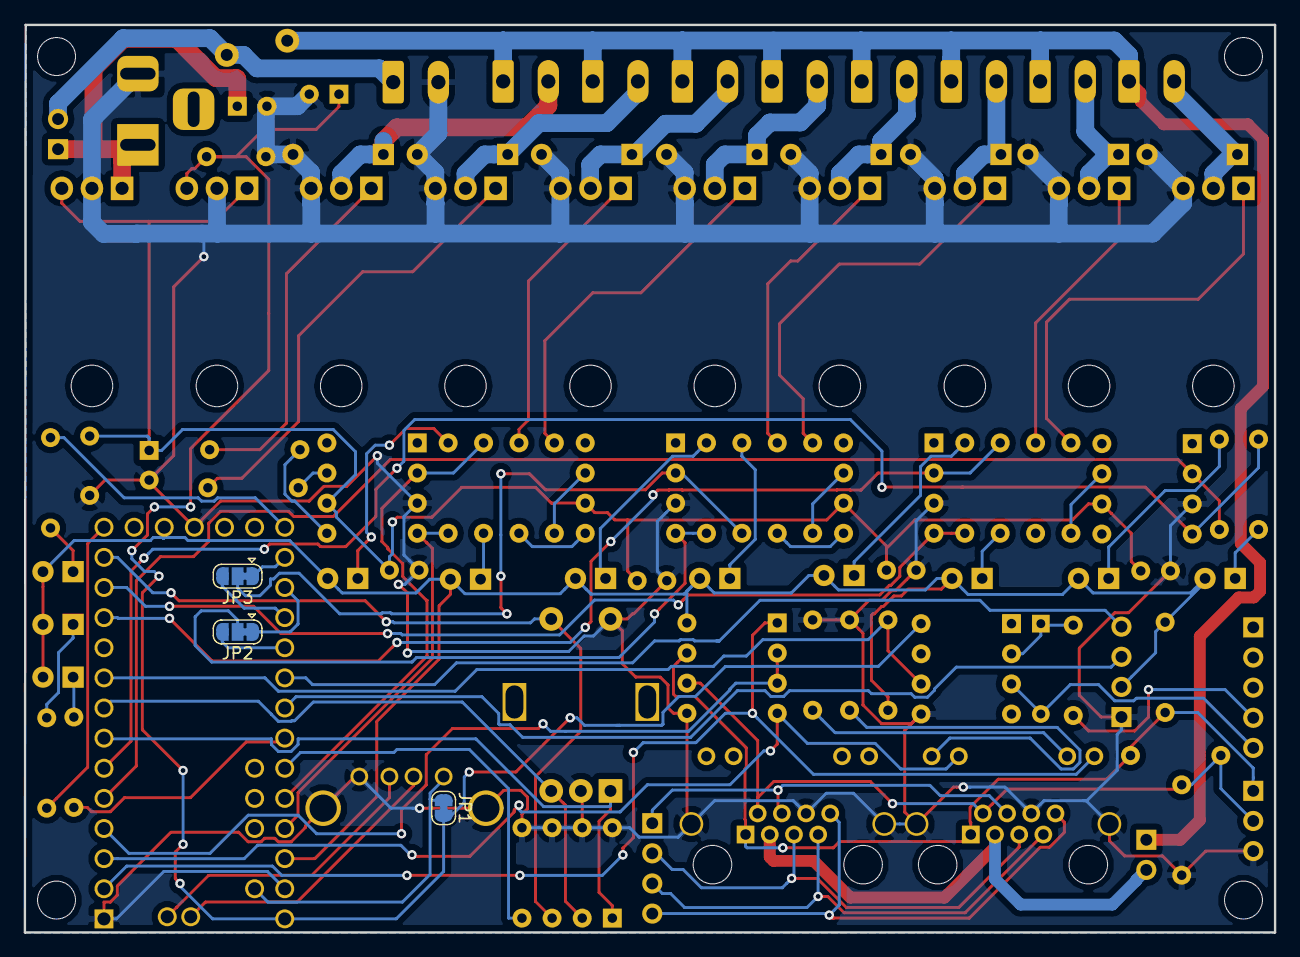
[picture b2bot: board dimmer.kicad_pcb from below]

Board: 2 copper layers, 105.4 x 76.5 mm, 101 parts (3 on the bottom side), 82 nets.

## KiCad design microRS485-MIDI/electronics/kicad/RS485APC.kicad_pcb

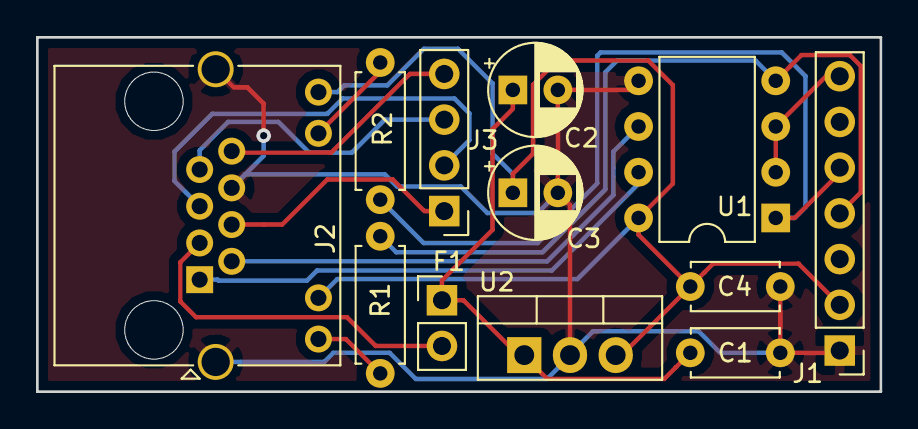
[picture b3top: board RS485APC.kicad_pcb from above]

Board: 2 copper layers, 46.9 x 19.7 mm, 12 parts (0 on the bottom side), 15 nets.

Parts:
C1, C4: 100n; C_Disc_D4.7mm_W2.5mm_P5.00mm
C2: 10uF; CP_Radial_D5.0mm_P2.50mm
C3: 100uF; CP_Radial_D5.0mm_P2.50mm
F1: Fuse; PinHeader_1x02_P2.54mm_Vertical
J1: APC220; PinHeader_1x07_P2.54mm_Vertical
J2: RJ45_LED_Shielded; RJ45_Amphenol_RJHSE538X
J3: Conn_01x04_Male; PinHeader_1x04_P2.54mm_Vertical
R1, R2: R; R_Axial_DIN0207_L6.3mm_D2.5mm_P7.62mm_Horizontal
U1: MAX485E; DIP-8_W7.62mm
U2: L7805; TO-220-3_Vertical

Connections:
/A: J2.2, U1.6
/B: J2.1, U1.7
/RXD: J1.4, R1.2, U1.4
/SET: J1.7, U1.2, U1.3
/TXD: J1.5, R2.2, U1.1
/Vbus: C1.1, C2.1, F1.1, U2.1
GND: C1.2, C2.2, C3.2, C4.2, J1.1, J2.6, J2.SH, U1.5, U2.2
unnamed: F1.2, J2.3
unnamed: J2.4, J3.1
unnamed: J2.5, J3.2
unnamed: J2.7, J3.3
unnamed: J2.8, J3.4
unnamed: J2.9, R1.1
unnamed: J2.11, R2.1
VCC: C3.1, C4.1, J1.2, J2.10, J2.12, U1.8, U2.3

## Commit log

2025-06-30 changed readme
2025-06-30 added files of former projects
2025-06-30 more readme
2025-06-30 minor
2025-08-24 added anarchitechno box project
2025-09-03 added tapperdiaper and picture
2025-09-03 RP2350 initial commit
2025-09-03 Logo!
2025-09-09 Block diagram proposal
2025-09-18 Large intermediate schematic push. Remaining todos are on frontpage.
2025-09-21 Stijn in de Trein
2025-09-21 meer Stijn in de Trein
2025-09-21 nog meer trein
2025-09-21 trein trein trein
2025-09-21 choo choooooo
2025-09-21 100mbit ethernet jack
2025-09-21 Step it up
2025-09-21 IPROPI comments on H-bridge
2025-09-22 3.3V 1A regulator on high & low side
2025-09-22 Layout drivers updated, more vias
2025-09-22 More room for VDC, added plane on L3
2025-09-24 Re-added 1.1V regulator. Removed 3.3VDDA for Ethernet. Increased clearances on layout a bit..
2025-09-24 Fix baord shape, because of RJ45
2025-09-24 Provision for backup DC/DC in case flyback doesn't work...
2025-09-24 Resized PCB with mounts at 125x125mm (suitable for 140mm PC fan), 4-pin fan connector added, changed 3.3VP to 5.0VP
2025-09-24 derp
2025-09-24 MIDI input using autosensing TRS midi jack
2025-10-05 added updated arduino sources for previous (atmega88) dimmer and RS485 interface
2025-10-05 sorry-accidently deleted these, no idea why
2025-10-09 Edwin's Connector Library
2025-10-09 Midi connector, ethernet connector imported with easyeda importer
2025-10-09 Schematic & PCB changes: - Cleaned up unnecessary electrolytic input capacitor flyback - Removed dual diode rectification on 5V, increased output capacitors - Feedback resistors DC/DCs set, enlarged 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
2025-10-09 Midi output buffer
2026-02-04 - Thermische berekening DRV8245 vs losse transistors - DRV8245 package gecorrigeerd naar TSSOP-28 - Layout aangepast om grotere package te passen - 1x GND output per kanaal - Waarschijnlijk geen 140m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
2026-02-06 - Logo Robot Theater lab - UART connector - RF antenne clearance aangepast - Reset/interrupt pins ethernet aangesloten
2026-03-25 BOM nagelopen, bestelklaar.
2026-03-25 10k W5500 on RSVD pin
2026-03-25 Productie notities voor JLC
2026-03-25 PCB DRC lijkt oke
2026-03-25 DRC check. Alleen nog courtyard clearances over
